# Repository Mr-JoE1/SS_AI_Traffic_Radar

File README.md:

<H1 align="center">SS_Project Backend Development </H1>
<p>
the project aims to design a full advanced radar system that can detect the car
lisence plate and other useful informations and facts.
</p>

## Repo Structure

  <H2> Firmware</H2><br>
  <p>contain the whole software that should be downloaded on the device .</p>

  <H2> Hardware</H2><br>
  <p>contain the whole schematics for the system.</p>

  <H2> ML</H2><br>
  <p>contain the whole AI models for the detection .</p>

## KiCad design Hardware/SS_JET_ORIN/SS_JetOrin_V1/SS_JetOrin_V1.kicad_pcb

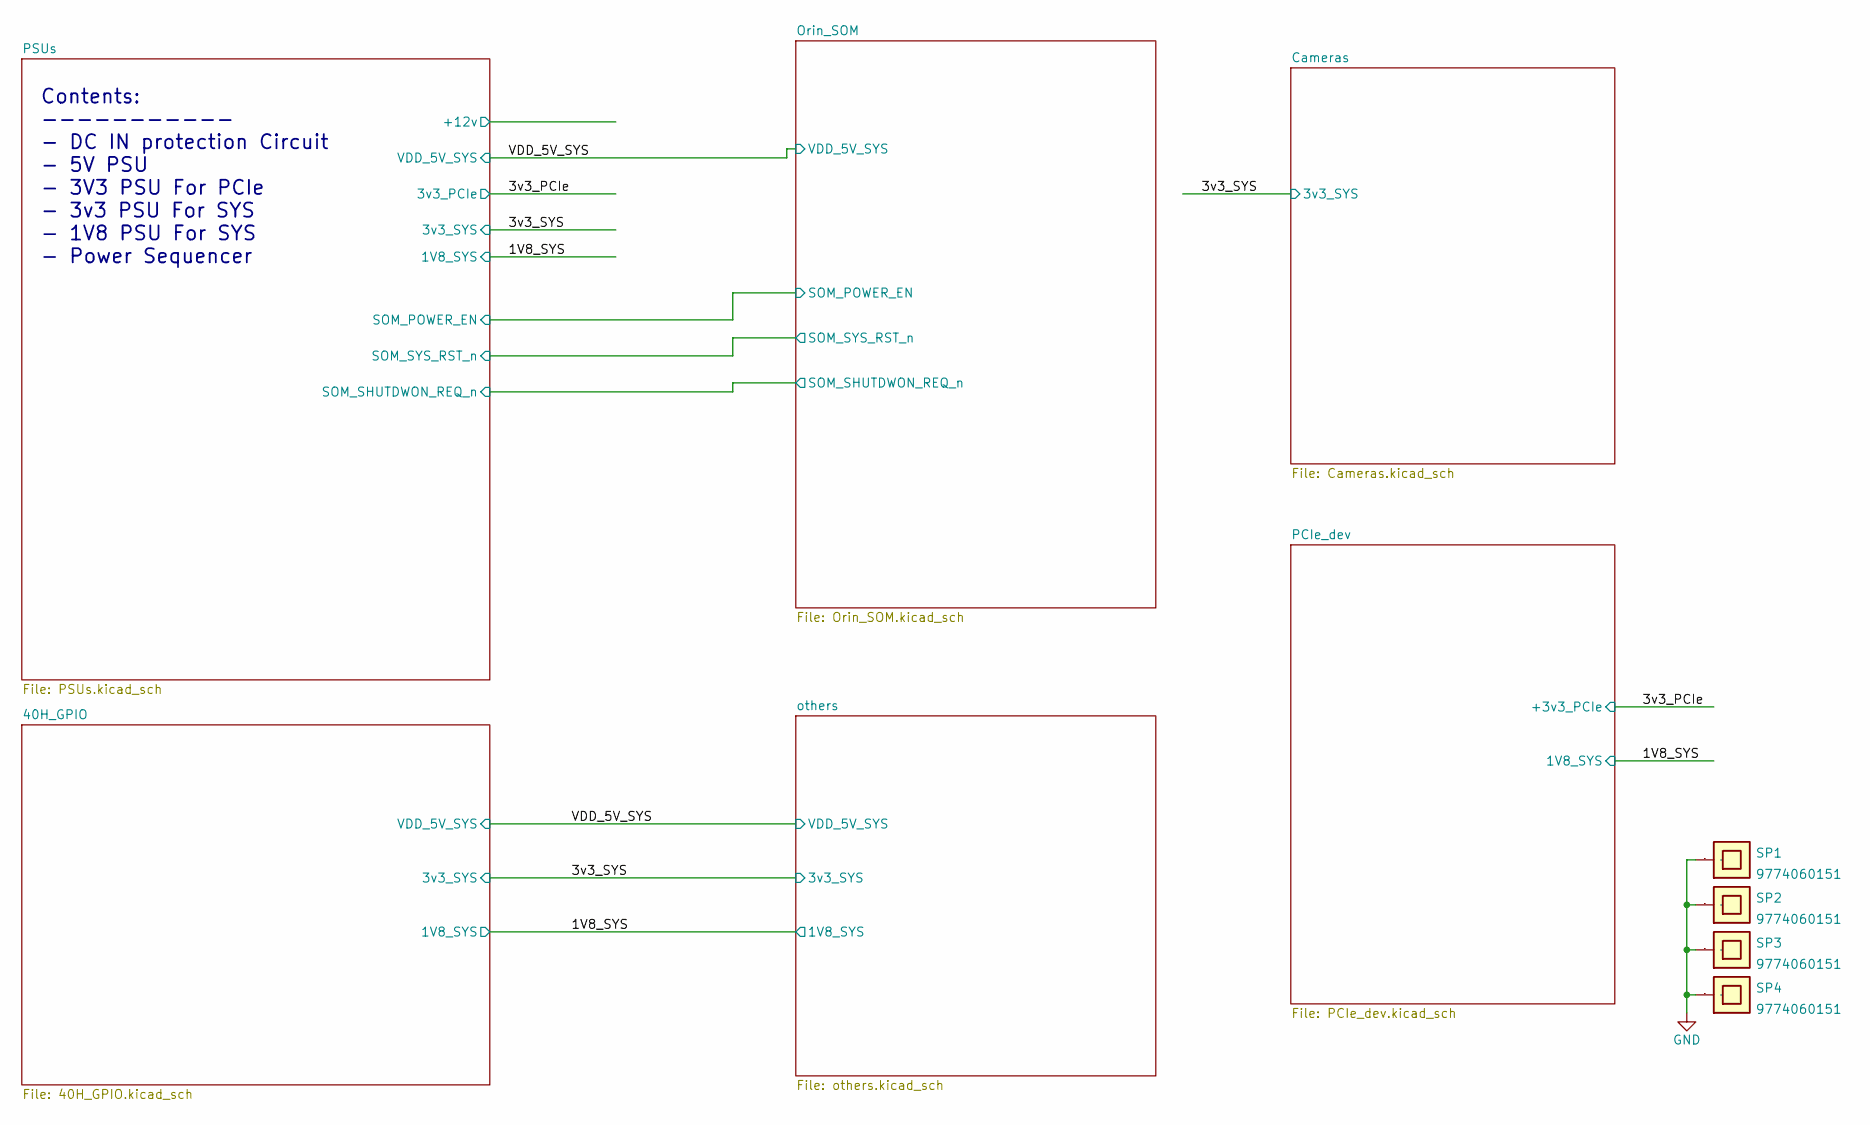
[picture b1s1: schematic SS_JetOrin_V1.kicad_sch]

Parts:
SP1, SP2, SP3, SP4: 9774060151; MPN 9774060151

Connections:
GND: SP1.1, SP2.1, SP3.1, SP4.1; also elsewhere on the board

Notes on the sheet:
Contents: ----------- - DC IN protection Circuit - 5V PSU - 3V3 PSU For PCIe - 3v3 PSU For SYS - 1V8 PSU For SYS - Power Sequencer

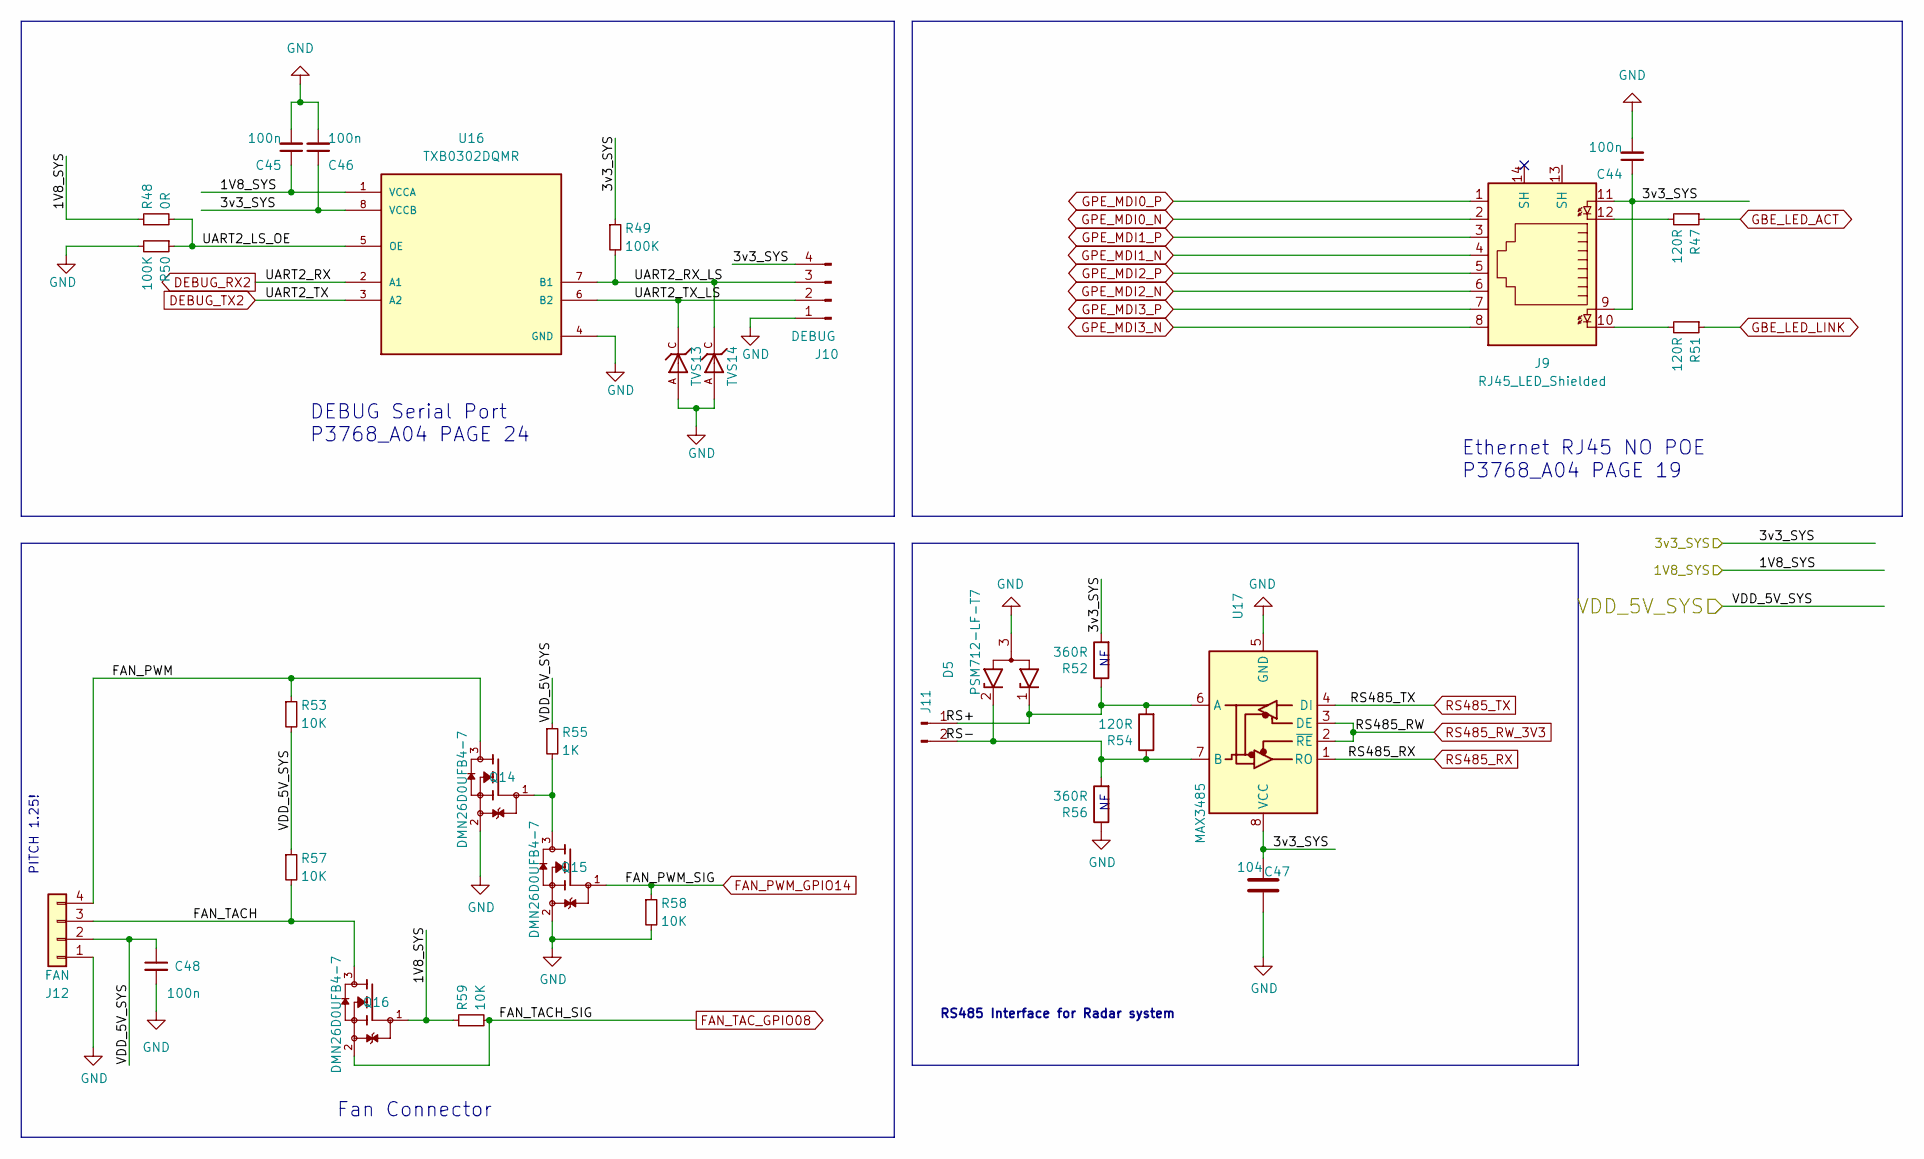
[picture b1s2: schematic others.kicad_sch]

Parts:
C44, C45, C46, C48: 100n; C_0201_0603Metric; LCSC C307380
C47: 104; C_0201_0603Metric; Part Description 0.1uF 10% 100V Ceramic Capacitor X5R 04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; LCSC C307380
D5: PSM712-LF-T7; SOT-23; LCSC C32677
J9: RJ45_LED_Shielded; RJ45-TH_R-RJ45R08P-C000; LCSC C386757
J10: DEBUG; PinHeader_1x04_P2.54mm_Vertical
J11: Conn_01x02_Male; PinHeader_1x02_P2.54mm_Vertical
J12: FAN; PinHeader_1x04_P2.54mm_Vertical; Part Description Wire-To-Board Connector, Right Angle, 2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; LCSC C5116483
Q14, Q15, Q16: DMN26D0UFB4-7; TRXDFN100X60X40-3N; PARTREV 12-2; LCSC C260867
R47, R51: 120R; R_0201_0603Metric; LCSC C295718
R48: 0R; R_0201_0603Metric; LCSC C106228
R49, R50: 100K; R_0201_0603Metric; LCSC C106224
R52, R56: 360R; R_0201_0603Metric; Part Description Resistor 1K M1005 1% 63mW; LCSC C2930003
R53, R57, R58, R59: 10K; R_0201_0603Metric; LCSC C106225
R54: 120R; R_0201_0603Metric; Part Description Resistor 1K M1005 1% 63mW; LCSC C295718
R55: 1K; R_0201_0603Metric; LCSC C131396
TVS13, TVS14: ESD9L5.0ST5G; DIOM1006X40N; PARTREV 7; LCSC C2682269
U16: TXB0302DQMR; IC_TXB0302DQMR; LCSC C2652938
U17: MAX3485; SOIC-8_3.9x4.9mm_P1.27mm; LCSC C9943

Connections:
/1V8_SYS: C45.1, Q16.1, R48.1, R59.1, U16.1 (VCCA); also elsewhere on the board
/3v3_SYS: C44.1, C46.1, C47.1, J9.9, J9.11, J10.4, R49.1, R52.2, U16.8 (VCCB), U17.8 (VCC); also elsewhere on the board
/VDD_5V_SYS: C48.1, J12.2, R53.2, R55.1, R57.1; also elsewhere on the board
/others/FAN_PWM: J12.4, Q14.3, R53.1
/others/FAN_TACH: J12.3, Q16.3, R57.2
/others/RS+: D5.1 (K1), J11.1, R52.1, R54.2, U17.6 (A)
/others/RS-: D5.2 (K2), J11.2, R54.1, R56.2, U17.7 (B)
/others/UART2_LS_OE: R48.2, R50.1, U16.5 (OE)
/others/UART2_RX_LS: J10.3, R49.2, TVS14.C, U16.7 (B1)
/others/UART2_TX_LS: J10.2, TVS13.C, U16.6 (B2)
DEBUG_RX2: U16.2 (A1); also elsewhere on the board
DEBUG_TX2: U16.3 (A2); also elsewhere on the board
FAN_PWM_GPIO14: Q15.1, R58.1; also elsewhere on the board
FAN_TAC_GPIO08: Q16.2, R59.2; also elsewhere on the board
GBE_LED_ACT: R47.1; also elsewhere on the board
GBE_LED_LINK: R51.1; also elsewhere on the board
GND: C44.2, C45.2, C46.2, C47.2, C48.2, D5.3 (A), J10.1, J12.1, Q14.2, Q15.2, R50.2, R56.1, R58.2, TVS13.A, TVS14.A, U16.4 (GND), U17.5 (GND); also elsewhere on the board
GPE_MDI0_N: J9.2; also elsewhere on the board
GPE_MDI0_P: J9.1; also elsewhere on the board
GPE_MDI1_N: J9.4; also elsewhere on the board
GPE_MDI1_P: J9.3; also elsewhere on the board
GPE_MDI2_N: J9.6; also elsewhere on the board
GPE_MDI2_P: J9.5; also elsewhere on the board
GPE_MDI3_N: J9.8; also elsewhere on the board
GPE_MDI3_P: J9.7; also elsewhere on the board
unnamed: J9.10, R51.2
unnamed: J9.12, R47.2
unnamed: Q14.1, Q15.3, R55.2
RS485_RW_3V3: U17.2 (~RE), U17.3 (DE); also elsewhere on the board
RS485_RX: U17.1 (RO); also elsewhere on the board
RS485_TX: U17.4 (DI); also elsewhere on the board

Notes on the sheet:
DEBUG Serial Port P3768_A04 PAGE 24
Ethernet RJ45 NO POE P3768_A04 PAGE 19
RS485 Interface for Radar system
Fan Connector
PITCH 1.25!

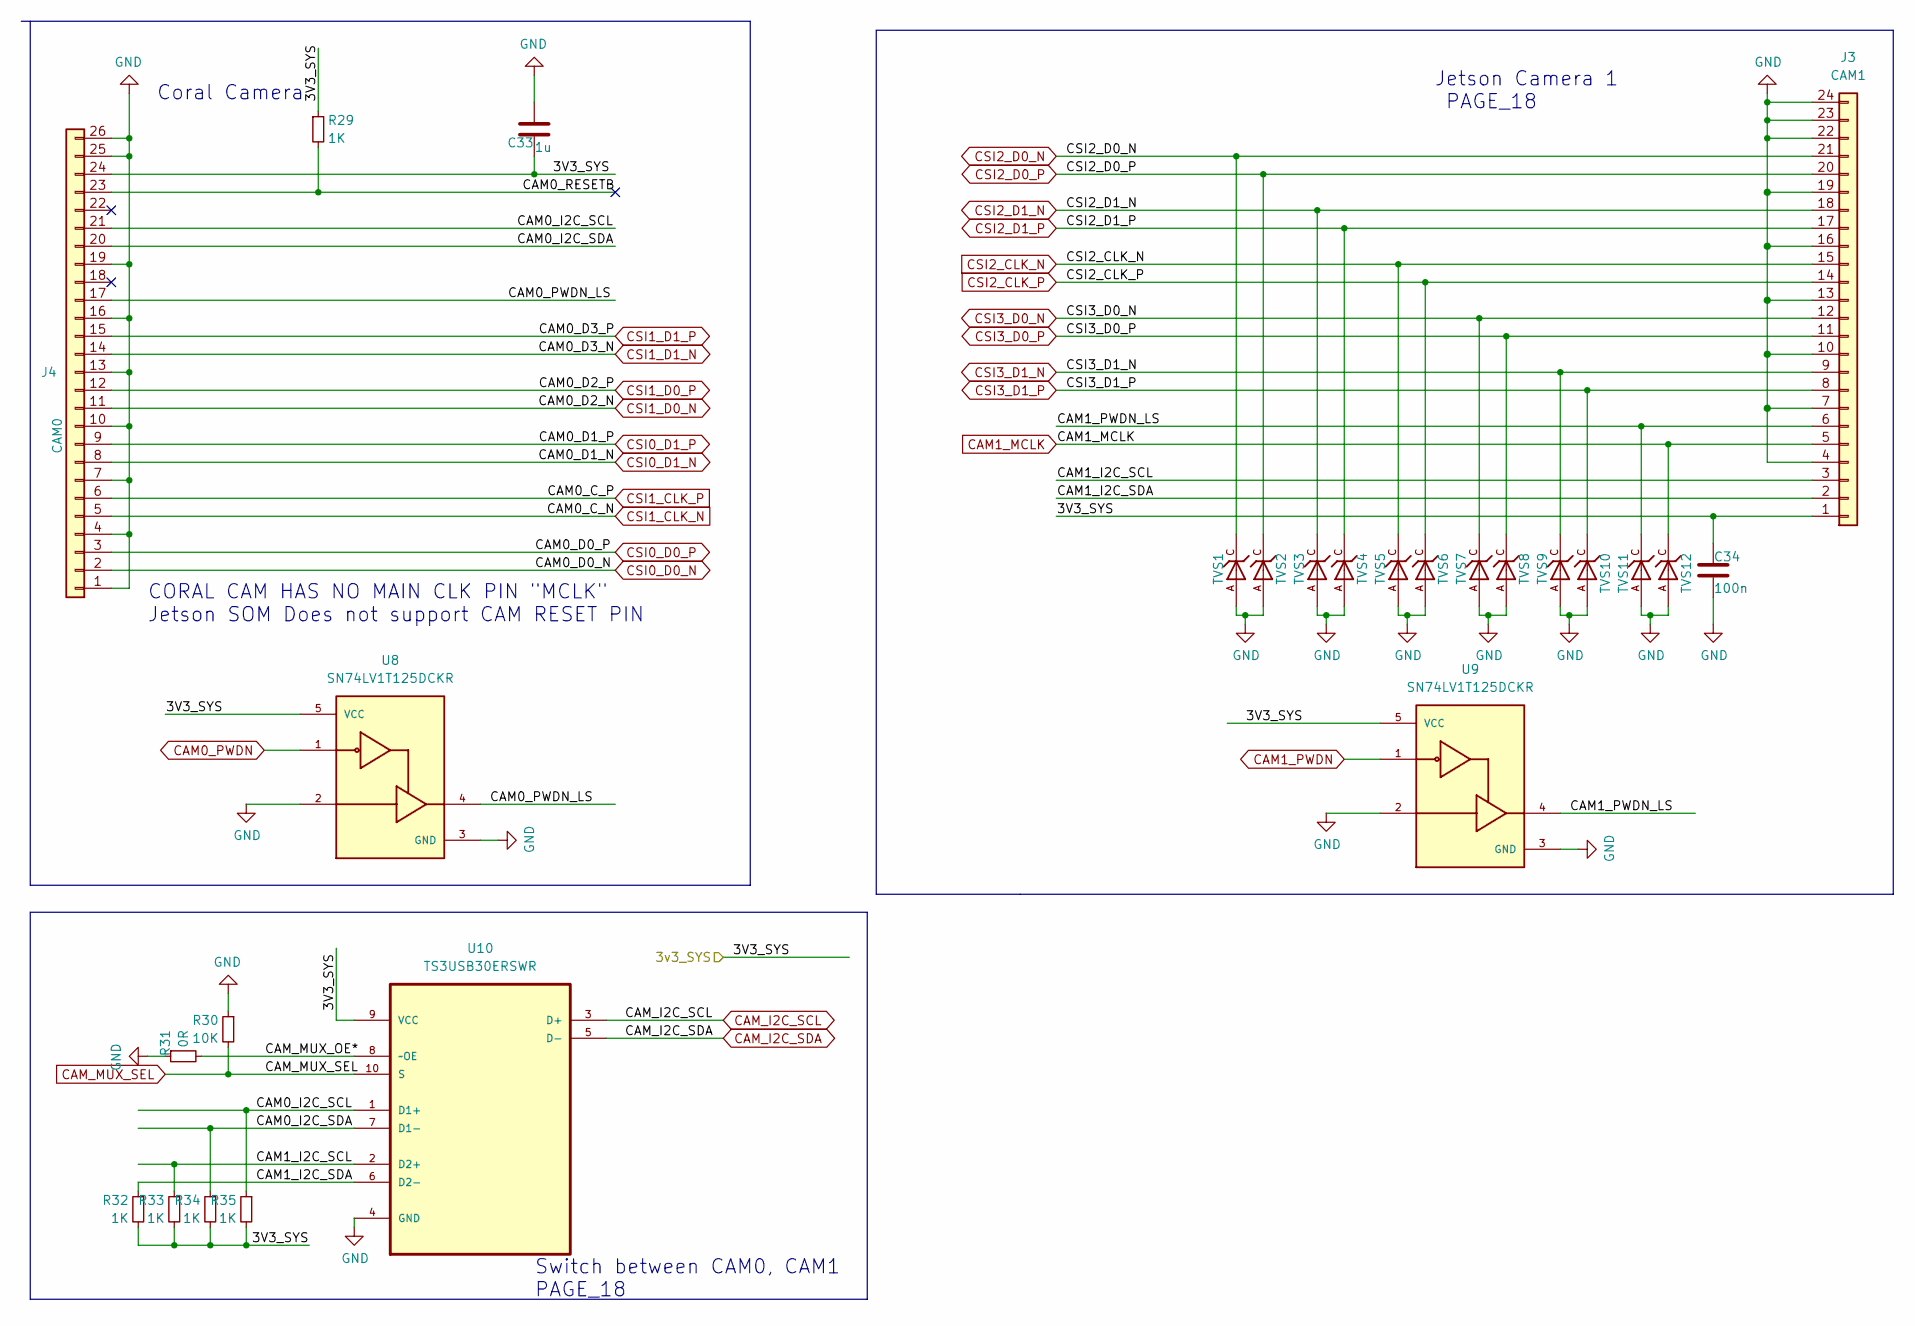
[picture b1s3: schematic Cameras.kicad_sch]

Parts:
C33: 1u; C_0201_0603Metric; LCSC C107005
C34: 100n; C_0201_0603Metric; Part Description 0.1uF 10% 100V Ceramic Capacitor X5R 04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; LCSC C307331
J3: CAM1; Hirose_FH12-22S-0.5SH_1x22-1MP_P0.50mm_Horizontal; LCSC C262668
J4: CAM0; FPC-SMD_P0.50-24P_QCHF-SM-H2.0; MPN FH12-24S-0.5SH(55); LCSC C262683
R29, R32, R33, R34, R35: 1K; R_0201_0603Metric; LCSC C131396
R30: 10K; R_0201_0603Metric; LCSC C106225
R31: 0R; R_0201_0603Metric; LCSC C106228
TVS1, TVS2, TVS3, TVS4, TVS5, TVS6, TVS7, TVS8, TVS9, TVS10, TVS11, TVS12: ESD9L5.0ST5G; DIOM1006X40N; PARTREV 7; LCSC C2682269
U8, U9: SN74LV1T125DCKR; SOT65P210X110-5N; PARTREV A; LCSC C75925
U10: TS3USB30ERSWR; QFN40P140X180X55-10N; MPN TS3USB30ERSWR

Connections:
/3v3_SYS: C33.1, C34.1, J3.1, J4.24, R29.1, R32.2, R33.2, R34.2, R35.2, U8.5 (VCC), U9.5 (VCC), U10.9 (VCC); also elsewhere on the board
/Cameras/CAM0_I2C_SCL: J4.21, R35.1, U10.1 (D1+)
/Cameras/CAM0_I2C_SDA: J4.20, R34.1, U10.7 (D1-)
/Cameras/CAM0_PWDN_LS: J4.17, U8.4
/Cameras/CAM0_RESETB: J4.23, R29.2
/Cameras/CAM1_I2C_SCL: J3.3, R33.1, U10.2 (D2+)
/Cameras/CAM1_I2C_SDA: J3.2, R32.1, U10.6 (D2-)
/Cameras/CAM1_PWDN_LS: J3.6, TVS11.C, U9.4
/Cameras/CAM_MUX_OE*: R31.2, U10.8 (~OE)
CAM0_PWDN: U8.1; also elsewhere on the board
CAM1_MCLK: J3.5, TVS12.C; also elsewhere on the board
CAM1_PWDN: U9.1; also elsewhere on the board
CAM_I2C_SCL: U10.3 (D+); also elsewhere on the board
CAM_I2C_SDA: U10.5 (D-); also elsewhere on the board
CAM_MUX_SEL: R30.2, U10.10 (S); also elsewhere on the board
CSI0_D0_N: J4.2; also elsewhere on the board
CSI0_D0_P: J4.3; also elsewhere on the board
CSI0_D1_N: J4.8; also elsewhere on the board
CSI0_D1_P: J4.9; also elsewhere on the board
CSI1_CLK_N: J4.5; also elsewhere on the board
CSI1_CLK_P: J4.6; also elsewhere on the board
CSI1_D0_N: J4.11; also elsewhere on the board
CSI1_D0_P: J4.12; also elsewhere on the board
CSI1_D1_N: J4.14; also elsewhere on the board
CSI1_D1_P: J4.15; also elsewhere on the board
CSI2_CLK_N: J3.15, TVS5.C; also elsewhere on the board
CSI2_CLK_P: J3.14, TVS6.C; also elsewhere on the board
CSI2_D0_N: J3.21, TVS1.C; also elsewhere on the board
CSI2_D0_P: J3.20, TVS2.C; also elsewhere on the board
CSI2_D1_N: J3.18, TVS3.C; also elsewhere on the board
CSI2_D1_P: J3.17, TVS4.C; also elsewhere on the board
CSI3_D0_N: J3.12, TVS7.C; also elsewhere on the board
CSI3_D0_P: J3.11, TVS8.C; also elsewhere on the board
CSI3_D1_N: J3.9, TVS9.C; also elsewhere on the board
CSI3_D1_P: J3.8, TVS10.C; also elsewhere on the board
GND: C33.2, C34.2, J3.4, J3.7, J3.10, J3.13, J3.16, J3.19, J3.22, J3.23, J3.24, J4.1, J4.4, J4.7, J4.10, J4.13, J4.16, J4.19, J4.25, J4.26, R30.1, R31.1, TVS1.A, TVS2.A, TVS3.A, TVS4.A, TVS5.A, TVS6.A, TVS7.A, TVS8.A, TVS9.A, TVS10.A, TVS11.A, TVS12.A, U8.2, U8.3 (GND), U9.2, U9.3 (GND), U10.4 (GND); also elsewhere on the board

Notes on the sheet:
CORAL CAM HAS NO MAIN CLK PIN "MCLK" Jetson SOM Does not support CAM RESET PIN
Coral Camera
Switch between CAM0, CAM1 PAGE_18
Jetson Camera 1 PAGE_18

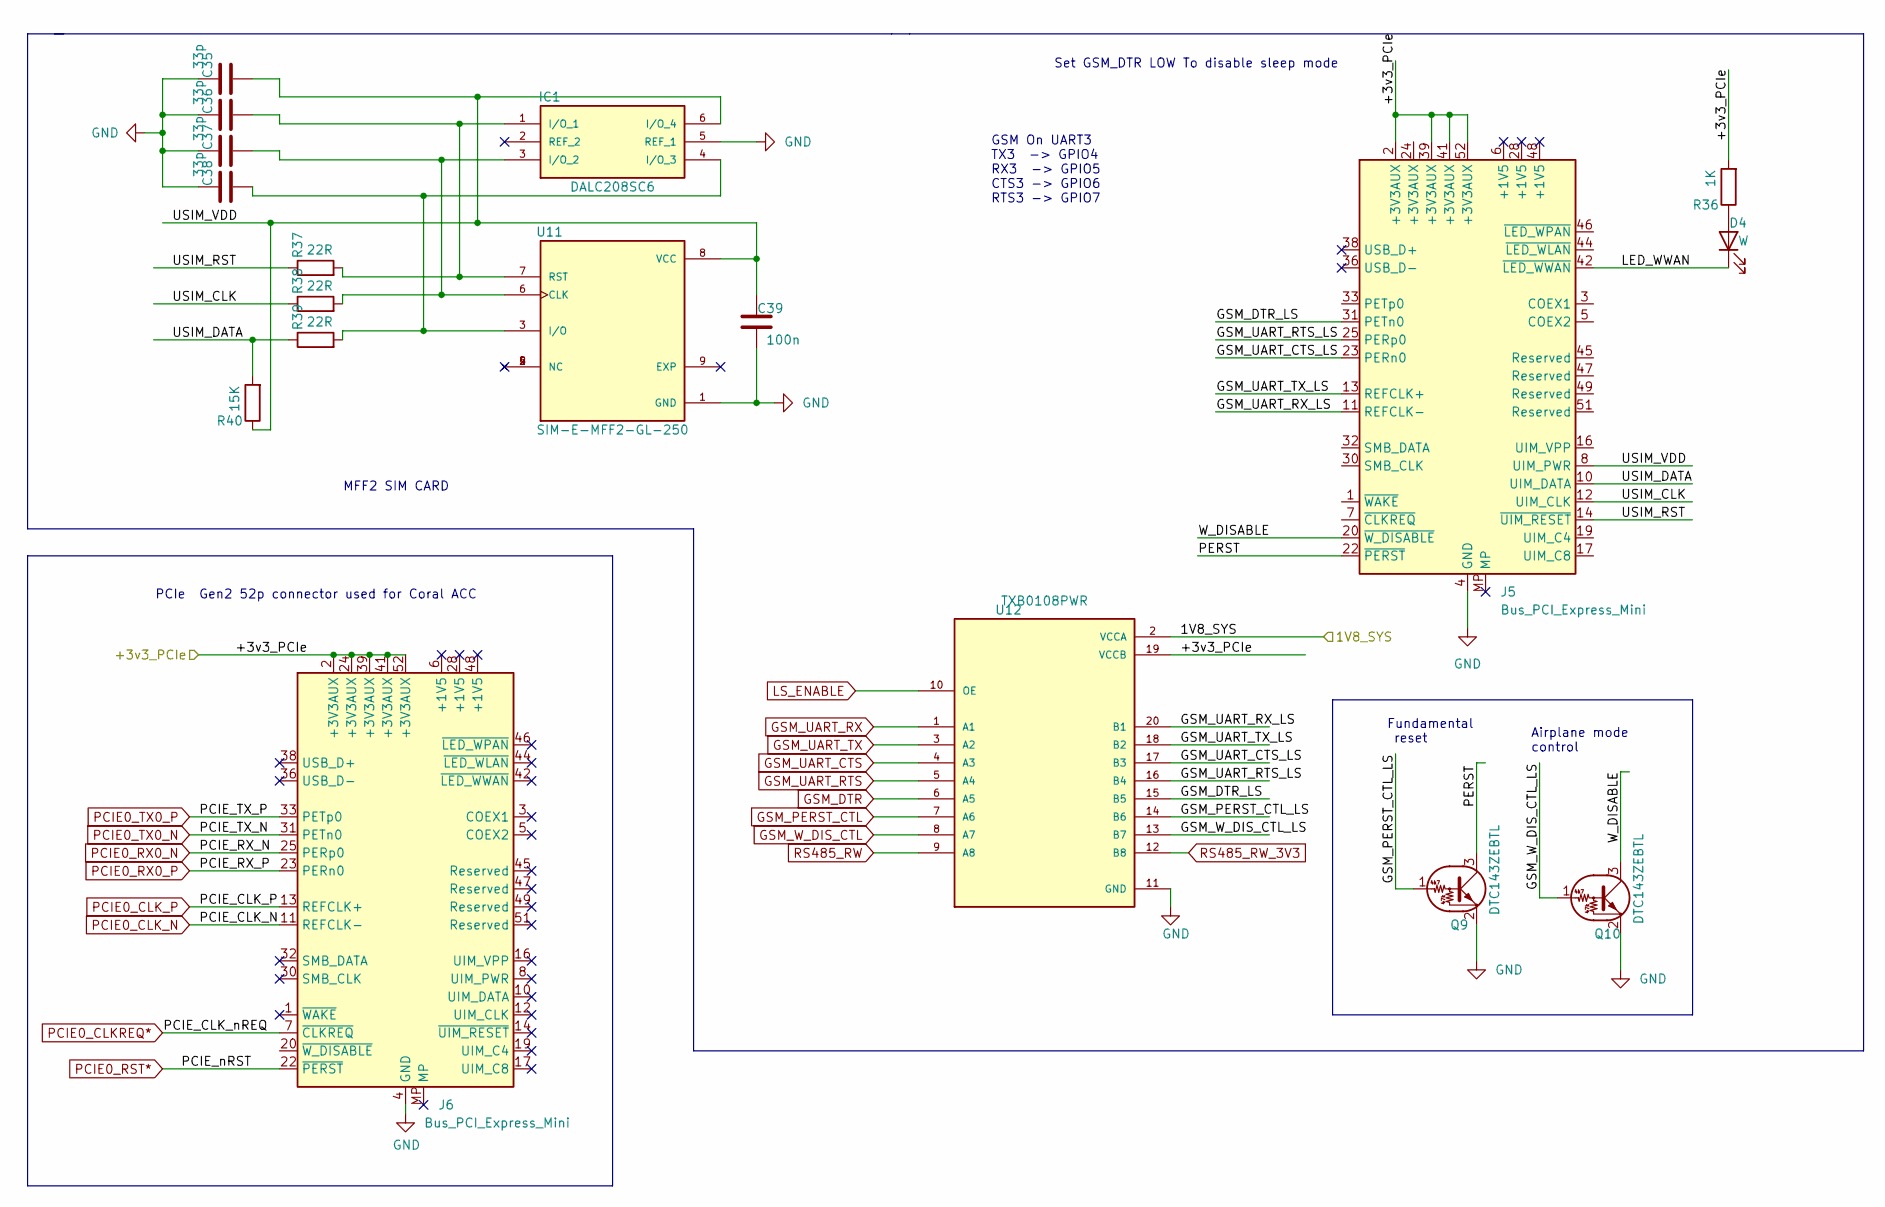
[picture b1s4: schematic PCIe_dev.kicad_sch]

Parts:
C35, C36, C37, C38: 33p; C_0201_0603Metric; LCSC C277477
C39: 100n; C_0201_0603Metric; Part Description 0.1uF 10% 100V Ceramic Capacitor X5R 04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; LCSC C307380
D4: W; LED_0402_1005Metric; LCSC C130724
IC1: DALC208SC6; SOT95P280X145-6N; MOUSER_PART_NUMBER 511-DALC208SC6
J5: Bus_PCI_Express_Mini; Quectel_EG25-G_Mini_PCIe; LCSC C266899
J6: Bus_PCI_Express_Mini; BUS_PCI_Express_Mini_Half; LCSC C266899
Q9, Q10: DTC143ZEBTL; SOTFL50P160X85-3N; LCSC C308696
R36: 1K; R_0201_0603Metric; LCSC C131396
R37, R38, R39: 22R; R_0201_0603Metric; LCSC C155743
R40: 15K; R_0201_0603Metric; LCSC C965337
U11: SIM-E-MFF2-GL-250; PSON127P500X600X82-9N; PARTREV V1.1
U12: TXB0108PWR; SOP65P640X120-20N; PARTREV H; LCSC C53406

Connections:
/1V8_SYS: U12.2 (VCCA); also elsewhere on the board
/3v3_PCIe: J5.2 (+3V3AUX), J5.39 (+3V3AUX), J5.41 (+3V3AUX), J5.52 (+3V3AUX), J6.2 (+3V3AUX), J6.24 (+3V3AUX), J6.39 (+3V3AUX), J6.41 (+3V3AUX), J6.52 (+3V3AUX), R36.2, U12.19 (VCCB); also elsewhere on the board
/PCIe_dev/GSM_DTR_LS: J5.31 (PETn0), U12.15 (B5)
/PCIe_dev/GSM_PERST_CTL_LS: Q9.1 (B), U12.14 (B6)
/PCIe_dev/GSM_UART_CTS_LS: J5.23 (PERn0), U12.17 (B3)
/PCIe_dev/GSM_UART_RTS_LS: J5.25 (PERp0), U12.16 (B4)
/PCIe_dev/GSM_UART_RX_LS: J5.11 (REFCLK-), U12.20 (B1)
/PCIe_dev/GSM_UART_TX_LS: J5.13 (REFCLK+), U12.18 (B2)
/PCIe_dev/GSM_W_DIS_CTL_LS: Q10.1 (B), U12.13 (B7)
/PCIe_dev/LED_WWAN: D4.1 (K), J5.42 (~LED_WWAN)
/PCIe_dev/PERST: J5.22 (~PERST), Q9.3 (C)
/PCIe_dev/USIM_CLK: J5.12 (UIM_CLK), R38.1
/PCIe_dev/USIM_DATA: J5.10 (UIM_DATA), R39.1, R40.2
/PCIe_dev/USIM_RST: J5.14 (~UIM_RESET), R37.1
/PCIe_dev/USIM_VDD: C35.2, C39.1, IC1.6 (I/O_4), J5.8 (UIM_PWR), R40.1, U11.8 (VCC)
/PCIe_dev/W_DISABLE: J5.20 (~W_DISABLE), Q10.3 (C)
GND: C35.1, C36.1, C37.1, C38.1, C39.2, IC1.5 (REF_1), J5.4 (GND), J5.9 (GND), J5.15 (GND), J5.18 (GND), J5.21 (GND), J5.26 (GND), J5.27 (GND), J5.29 (GND), J5.34 (GND), J5.35 (GND), J5.37 (GND), J5.40 (GND), J5.43 (GND), J5.50 (GND), J6.4 (GND), J6.9 (GND), J6.15 (GND), J6.18 (GND), J6.21 (GND), J6.26 (GND), J6.27 (GND), J6.29 (GND), J6.34 (GND), J6.35 (GND), J6.37 (GND), J6.40 (GND), J6.43 (GND), J6.50 (GND), Q9.2 (E), Q10.2 (E), U11.1 (GND), U12.11 (GND); also elsewhere on the board
GSM_DTR: U12.6 (A5); also elsewhere on the board
GSM_PERST_CTL: U12.7 (A6); also elsewhere on the board
GSM_UART_CTS: U12.4 (A3); also elsewhere on the board
GSM_UART_RTS: U12.5 (A4); also elsewhere on the board
GSM_UART_RX: U12.1 (A1); also elsewhere on the board
GSM_UART_TX: U12.3 (A2); also elsewhere on the board
GSM_W_DIS_CTL: U12.8 (A7); also elsewhere on the board
LS_ENABLE: U12.10 (OE); also elsewhere on the board
unnamed: C36.2, IC1.1 (I/O_1), R37.2, U11.7 (RST)
unnamed: C37.2, IC1.3 (I/O_2), R38.2, U11.6 (CLK)
unnamed: C38.2, IC1.4 (I/O_3), R39.2, U11.3 (I/O)
unnamed: D4.2 (A), R36.1
PCIE0_CLKREQ*: J6.7 (~CLKREQ); also elsewhere on the board
PCIE0_CLK_N: J6.11 (REFCLK-); also elsewhere on the board
PCIE0_CLK_P: J6.13 (REFCLK+); also elsewhere on the board
PCIE0_RST*: J6.22 (~PERST); also elsewhere on the board
PCIE0_RX0_N: J6.25 (PERp0); also elsewhere on the board
PCIE0_RX0_P: J6.23 (PERn0); also elsewhere on the board
PCIE0_TX0_N: J6.31 (PETn0); also elsewhere on the board
PCIE0_TX0_P: J6.33 (PETp0); also elsewhere on the board
RS485_RW: U12.9 (A8); also elsewhere on the board
RS485_RW_3V3: U12.12 (B8); also elsewhere on the board

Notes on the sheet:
GSM On UART3 TX3 -> GPIO4 RX3 -> GPIO5 CTS3 -> GPIO6 RTS3 -> GPIO7
Fundamental reset
Airplane mode control
PCIe Gen2 52p connector used for Coral ACC
Set GSM_DTR LOW To disable sleep mode
MFF2 SIM CARD

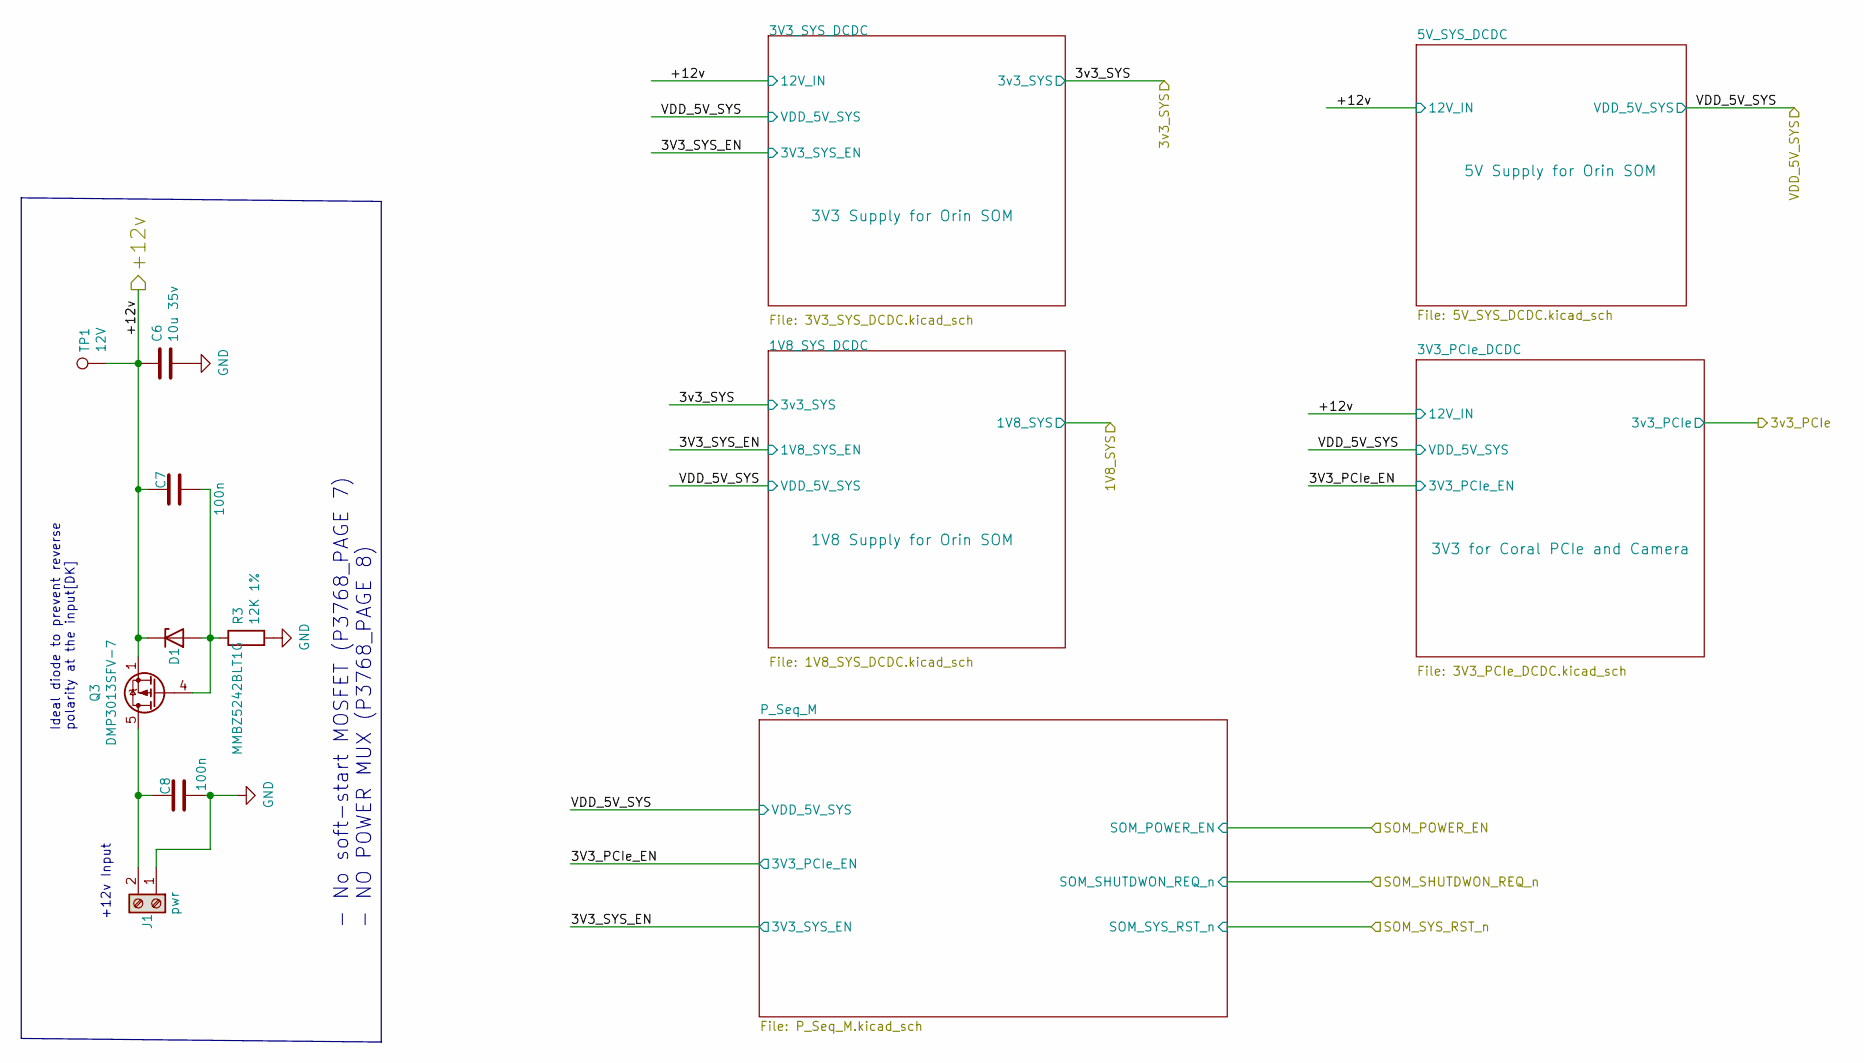
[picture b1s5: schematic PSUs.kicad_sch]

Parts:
C6: 10u 35v; C_0603_1608Metric; LCSC C194427
C7, C8: 100n; C_0201_0603Metric; Part Description 0.1uF 10% 100V Ceramic Capacitor X5R 04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; LCSC C307380
D1: MMBZ5242BLT1G; SOT-23; Part Description Zener Diode 12V 225mW 5% Surface Mount 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; LCSC C236184
J1: pwr; TerminalBlock_bornier-2_P5.08mm; LCSC C430455
Q3: DMP3013SFV-7; Diodes_PowerDI3333-8; Part Description DMP3013SFV-7 - Power MOSFET, P Channel,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; LCSC C264098
R3: 12K 1%; R_0201_0603Metric; Part Description Resistor 12K M1005 1% 63mW; LCSC C226413
TP1: 12V; TestPoint_Pad_D1.0mm

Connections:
/PSUs/+12v: C6.1, C7.1, D1.3 (K), Q3.1 (S), Q3.2 (S), Q3.3 (S), TP1.1; also elsewhere on the board
GND: C6.2, C8.2, J1.1, R3.2; also elsewhere on the board
unnamed: C7.2, D1.1 (A), Q3.4 (G), R3.1
unnamed: C8.1, J1.2, Q3.5 (D)

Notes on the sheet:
- No soft-start MOSFET (P3768_PAGE 7) - NO POWER MUX (P3768_PAGE 8)
Ideal diode to prevent reverse polarity at the input[DK]
+12v Input

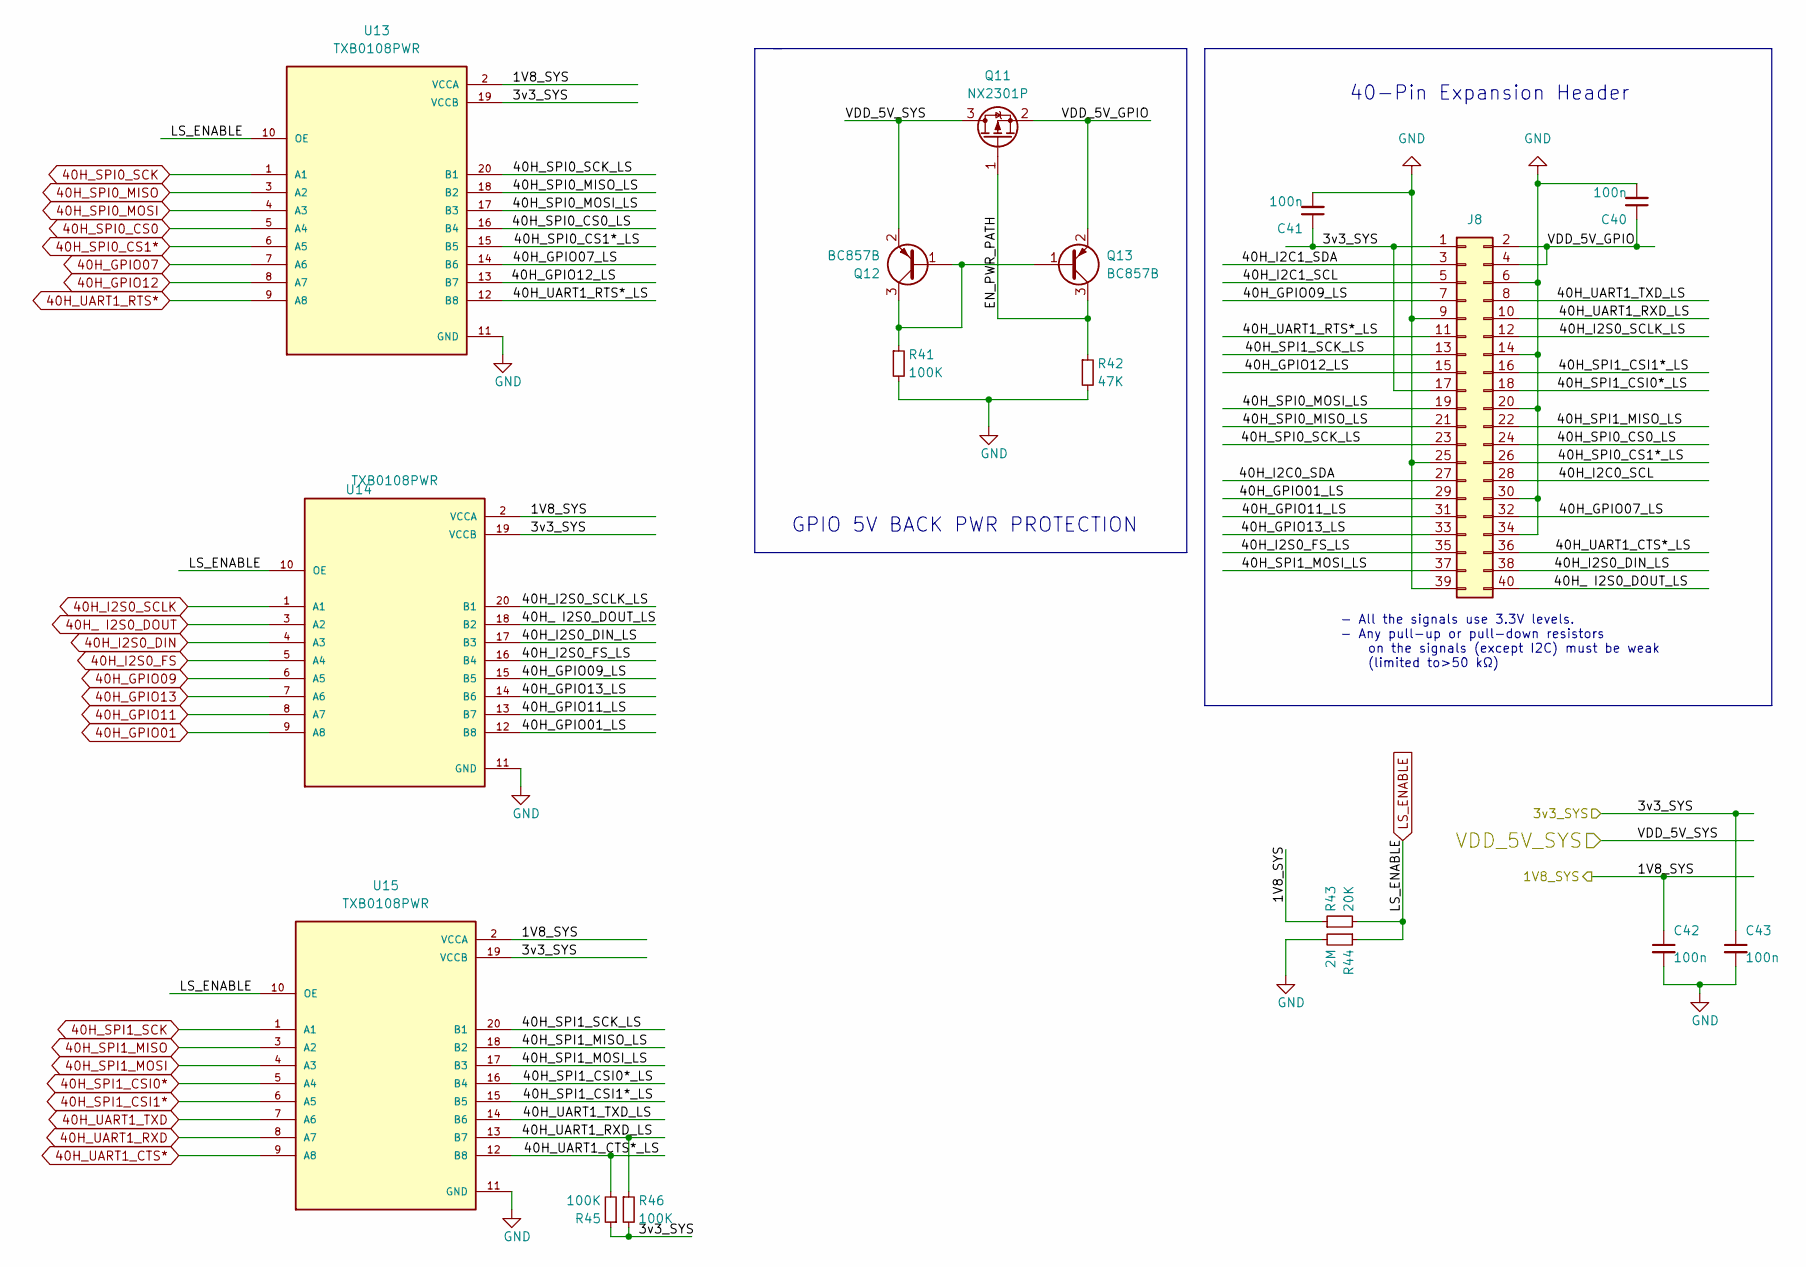
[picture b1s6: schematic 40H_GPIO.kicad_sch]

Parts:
C40, C41, C42, C43: 100n; C_0201_0603Metric; LCSC C307380
J8: Conn_02x20_Odd_Even; PinHeader_2x20_P2.54mm_Vertical
Q11: NX2301P; SOT-23; LCSC C191273
Q12, Q13: BC857B; SOT-23; LCSC C556165
R41, R45, R46: 100K; R_0201_0603Metric; LCSC C106224
R42: 47K; R_0201_0603Metric; LCSC C138139
R43: 20K; R_0201_0603Metric; LCSC C295787
R44: 2M; R_0201_0603Metric; LCSC C106228
U13, U14, U15: TXB0108PWR; SOP65P640X120-20N; PARTREV H; LCSC C53406

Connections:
40H_ I2S0_DOUT: U14.3 (A2); also elsewhere on the board
40H_GPIO01: U14.9 (A8); also elsewhere on the board
40H_GPIO07: U13.7 (A6); also elsewhere on the board
40H_GPIO09: U14.6 (A5); also elsewhere on the board
40H_GPIO11: U14.8 (A7); also elsewhere on the board
40H_GPIO12: U13.8 (A7); also elsewhere on the board
40H_GPIO13: U14.7 (A6); also elsewhere on the board
40H_I2S0_DIN: U14.4 (A3); also elsewhere on the board
40H_I2S0_FS: U14.5 (A4); also elsewhere on the board
40H_I2S0_SCLK: U14.1 (A1); also elsewhere on the board
40H_SPI0_CS0: U13.5 (A4); also elsewhere on the board
40H_SPI0_CS1*: U13.6 (A5); also elsewhere on the board
40H_SPI0_MISO: U13.3 (A2); also elsewhere on the board
40H_SPI0_MOSI: U13.4 (A3); also elsewhere on the board
40H_SPI0_SCK: U13.1 (A1); also elsewhere on the board
40H_SPI1_CSI0*: U15.5 (A4); also elsewhere on the board
40H_SPI1_CSI1*: U15.6 (A5); also elsewhere on the board
40H_SPI1_MISO: U15.3 (A2); also elsewhere on the board
40H_SPI1_MOSI: U15.4 (A3); also elsewhere on the board
40H_SPI1_SCK: U15.1 (A1); also elsewhere on the board
40H_UART1_CTS*: U15.9 (A8); also elsewhere on the board
40H_UART1_RTS*: U13.9 (A8); also elsewhere on the board
40H_UART1_RXD: U15.8 (A7); also elsewhere on the board
40H_UART1_TXD: U15.7 (A6); also elsewhere on the board
/1V8_SYS: C42.1, R43.1, U13.2 (VCCA), U14.2 (VCCA), U15.2 (VCCA); also elsewhere on the board
/3v3_SYS: C41.1, C43.1, J8.1, J8.17, R45.1, R46.2, U13.19 (VCCB), U14.19 (VCCB), U15.19 (VCCB); also elsewhere on the board
/40H_GPIO/40H_ I2S0_DOUT_LS: J8.40, U14.18 (B2)
/40H_GPIO/40H_GPIO01_LS: J8.29, U14.12 (B8)
/40H_GPIO/40H_GPIO07_LS: J8.32, U13.14 (B6)
/40H_GPIO/40H_GPIO09_LS: J8.7, U14.15 (B5)
/40H_GPIO/40H_GPIO11_LS: J8.31, U14.13 (B7)
/40H_GPIO/40H_GPIO12_LS: J8.15, U13.13 (B7)
/40H_GPIO/40H_GPIO13_LS: J8.33, U14.14 (B6)
/40H_GPIO/40H_I2C0_SCL: J8.28
/40H_GPIO/40H_I2C0_SDA: J8.27
/40H_GPIO/40H_I2C1_SCL: J8.5
/40H_GPIO/40H_I2C1_SDA: J8.3
/40H_GPIO/40H_I2S0_DIN_LS: J8.38, U14.17 (B3)
/40H_GPIO/40H_I2S0_FS_LS: J8.35, U14.16 (B4)
/40H_GPIO/40H_I2S0_SCLK_LS: J8.12, U14.20 (B1)
/40H_GPIO/40H_SPI0_CS0_LS: J8.24, U13.16 (B4)
/40H_GPIO/40H_SPI0_CS1*_LS: J8.26, U13.15 (B5)
/40H_GPIO/40H_SPI0_MISO_LS: J8.21, U13.18 (B2)
/40H_GPIO/40H_SPI0_MOSI_LS: J8.19, U13.17 (B3)
/40H_GPIO/40H_SPI0_SCK_LS: J8.23, U13.20 (B1)
/40H_GPIO/40H_SPI1_CSI0*_LS: J8.18, U15.16 (B4)
/40H_GPIO/40H_SPI1_CSI1*_LS: J8.16, U15.15 (B5)
/40H_GPIO/40H_SPI1_MISO_LS: J8.22, U15.18 (B2)
/40H_GPIO/40H_SPI1_MOSI_LS: J8.37, U15.17 (B3)
/40H_GPIO/40H_SPI1_SCK_LS: J8.13, U15.20 (B1)
/40H_GPIO/40H_UART1_CTS*_LS: J8.36, R45.2, U15.12 (B8)
/40H_GPIO/40H_UART1_RTS*_LS: J8.11, U13.12 (B8)
/40H_GPIO/40H_UART1_RXD_LS: J8.10, R46.1, U15.13 (B7)
/40H_GPIO/40H_UART1_TXD_LS: J8.8, U15.14 (B6)
/40H_GPIO/EN_PWR_PATH: Q11.1 (G), Q13.3 (C), R42.1
/40H_GPIO/VDD_5V_GPIO: C40.1, J8.2, J8.4, Q11.2 (S), Q13.2 (E)
/VDD_5V_SYS: Q11.3 (D), Q12.2 (E); also elsewhere on the board
GND: C40.2, C41.2, C42.2, C43.2, J8.6, J8.9, J8.14, J8.20, J8.25, J8.30, J8.34, J8.39, R41.2, R42.2, R44.2, U13.11 (GND), U14.11 (GND), U15.11 (GND); also elsewhere on the board
LS_ENABLE: R43.2, R44.1, U13.10 (OE), U14.10 (OE), U15.10 (OE); also elsewhere on the board
unnamed: Q12.1 (B), Q12.3 (C), Q13.1 (B), R41.1

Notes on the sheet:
40-Pin Expansion Header
GPIO 5V BACK PWR PROTECTION
- All the signals use 3.3V levels. - Any pull-up or pull-down resistors on the signals (except I2C) must be weak (limited to>50 kΩ)

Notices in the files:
parts and their libraries:
Copyright 2016 Accelerated Designs. All rights reserved.
